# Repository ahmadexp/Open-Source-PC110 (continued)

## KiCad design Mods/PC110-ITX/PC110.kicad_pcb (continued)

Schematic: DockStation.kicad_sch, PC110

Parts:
C1: DNP; C_0402_1005Metric; not fitted
C2, C235, C237, C239, C265: 150nF; C_0402_1005Metric
C3, C7, C91, C93: 100nF; C_0402_1005Metric
C4: 1nF; C_0402_1005Metric
C86, C88: 180nF; C_0402_1005Metric
C89: 470nF; C_0603_1608Metric
C90, C92, C198, C243: 120nF; C_0402_1005Metric
C163, C167, C170, C199: 220pF; C_0402_1005Metric
C168, C238: 1uF; C_0603_1608Metric
C197, C240: 300nF; C_0603_1608Metric
C200, C201: 10uF; C_1206_3216Metric
C202: 150nF; C_0603_1608Metric
D1: 3D
D39, D55: s.3 5F; Diode
D52, D53, D54, D56, D57: K; SOT-416
D59: 3D; SOT-416L
EM5: R-array
F2: 1.0A; Fuse_1206_3216Metric
F3: 0.5A; Fuse_1206_3216Metric
J1: PS2
J8: Modem-Connector
J13: Docking Port
L1: 1.5uH; L_0603_1608Metric
L12: 300nH; L_0805_2012Metric
Q24: 6D; SOT-23
Q25, Q33, Q34: BH RT; SOT-89-3
Q32: 8B; SOT-416
R4: 4.7k; R_0402_1005Metric
R8: 300; R_0402_1005Metric
R122, R123, R124, R125, R127, R130, R135, R139, R144, R183, R187, R189, R190, R191, R194, R228, R302, R303, R305, R306, R307, R309, R311: 470k; R_0402_1005Metric
R181, R188, R192, R193, R289: 10k; R_0402_1005Metric
R230: 0; R_0805_2012Metric
R231: 0; R_0603_1608Metric
R238: 56; R_0603_1608Metric
R241: 8.2; R_1206_3216Metric_Pad1.30x1.75mm_HandSolder
R242: 7.5k; R_0402_1005Metric
R291, R297: 220; R_0402_1005Metric
R293: 22k; R_0402_1005Metric
R294: 1.2k; R_0402_1005Metric
RA2: 10k; R-array
U1: EA; SOT-353
U2: 7W32; sso-8
U3: HSDL-1000 X03; IRDA
U20: 7W14; sso-8
U26: 7W126; sso-8
U57: SN74LVT125; TSSOP-14_4.4x5mm_P0.65mm
U64: SN74LV126; TSSOP-14_4.4x5mm_P0.65mm
U71: SN74LV32; TSSOP-14_4.4x5mm_P0.65mm

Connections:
Dock_PWR_IN-: J13.53 (J13_53), J13.54 (J13_53), J13.55 (J13_53), J13.56 (J13_53), J13.57 (J13_53); also elsewhere on the board
EN_RS232: J13.79 (EN_RS232); also elsewhere on the board
Enable_IRDA_Buf: Q24.1 (B), R242.2, U26.1 (C), U26.7 (~PRE), U57.4, U57.10; also elsewhere on the board
FDC_ACK#: J13.71 (ACK#); also elsewhere on the board
FDC_AUTOFD#: J13.73 (AUTOFD#); also elsewhere on the board
FDC_BUSY: J13.22 (BUSY); also elsewhere on the board
FDC_CTS1#: J8.8 (CTS1#), R191.1; also elsewhere on the board
FDC_CTS2#: J13.82 (CTS2#), R303.2; also elsewhere on the board
FDC_DCD1#: J8.4 (DCD1#), R187.1; also elsewhere on the board
FDC_DCD2#: J13.17 (DCD2#), R309.2; also elsewhere on the board
FDC_DIR#: J13.7 (FDC_DIR#); also elsewhere on the board
FDC_DRATE0: R302.2, U57.2; also elsewhere on the board
FDC_DRATE1: R306.2, U57.12; also elsewhere on the board
FDC_DSKCHG#: J13.12 (FDC_DSKCHG#), R122.2; also elsewhere on the board
FDC_DSR1: J8.7 (DSR1), R189.1; also elsewhere on the board
FDC_DSR2#: J13.84 (DSR2#), R305.2; also elsewhere on the board
FDC_DTR1#: R192.1, U64.9; also elsewhere on the board
FDC_DTR2#: J13.20 (DTR2#); also elsewhere on the board
FDC_ERROR#: J13.77 (ERROR#); also elsewhere on the board
FDC_HDSEL#: J13.11 (FDC_HDSEL#); also elsewhere on the board
FDC_INIT#: J13.72 (INIT#); also elsewhere on the board
FDC_IRRX_RXD2: U26.3 (~Q), U57.8; also elsewhere on the board
FDC_IRTX_TXD2: R183.2, U26.2 (D), U57.5; also elsewhere on the board
FDC_PD0: J13.30 (PD0); also elsewhere on the board
FDC_PD1: J13.29 (PD1); also elsewhere on the board
FDC_PD2: J13.28 (PD2); also elsewhere on the board
FDC_PD3: J13.27 (PD3); also elsewhere on the board
FDC_PD4: J13.26 (PD4); also elsewhere on the board
FDC_PD5: J13.25 (PD5); also elsewhere on the board
FDC_PD6: J13.76 (PD6); also elsewhere on the board
FDC_PD7: J13.24 (PD7); also elsewhere on the board
FDC_PE: J13.78 (PE); also elsewhere on the board
FDC_RDATA#: J13.91 (FDC_RDATA#), R307.2; also elsewhere on the board
FDC_RI1#: J8.5 (RI1#), R190.1; also elsewhere on the board
FDC_RI2#: J13.81 (RI2#), R311.1; also elsewhere on the board
FDC_RTS1#: R193.1, U64.5; also elsewhere on the board
FDC_RTS2#: J13.83 (RTS2#); also elsewhere on the board
FDC_RXD1: J8.10 (RXD1), R194.1; also elsewhere on the board
FDC_SLCT: J13.23 (SLCT); also elsewhere on the board
FDC_SLCTIN#: J13.74 (SLCTIN#); also elsewhere on the board
FDC_STEP#: J13.94 (FDC_STEP#); also elsewhere on the board
FDC_STROBE#: J13.31 (STROBE#); also elsewhere on the board
FDC_TRK0#: J13.9 (FDC_TRK0), R124.2; also elsewhere on the board
FDC_TXD1: R188.1, U64.2; also elsewhere on the board
FDC_TXD2_EN: R8.1, U2.5, U57.6
FDC_UART1_EN: U64.1, U64.4, U64.10; also elsewhere on the board
FDC_WDATA#: J13.8 (FDC_WDATA#); also elsewhere on the board
FDC_WGATE#: J13.93 (FDC_WGATE#); also elsewhere on the board
FDC_WRTPRT#: J13.10 (FDC_WRTPRT#), R125.1; also elsewhere on the board
FDD_Bowman: J13.90 (FDD_Bowman), R144.2; also elsewhere on the board
FDD_DRSEL: J13.5 (FDD_DRSEL); also elsewhere on the board
FDD_INDEX#: J13.4 (FDD_INDEX#), R123.2; also elsewhere on the board
FDD_MOTEN: J13.6 (FDD_MOTEN); also elsewhere on the board
FDD_Pluto1: J13.98 (FDD_Pluto1); also elsewhere on the board
FDD_Pluto2: J13.97 (FDD_Pluto2); also elsewhere on the board
FDD_Pluto3: J13.95 (FDD_Pluto3); also elsewhere on the board
FDD_Pluto4: J13.92 (FDD_Pluto4); also elsewhere on the board
GND: C1.1 (+), C2.2 (-), C3.2 (-), C4.2 (-), C7.2 (-), C86.2 (-), C88.1 (+), C90.1 (+), C91.2 (-), C92.1 (+), C93.2 (-), C163.1 (+), C167.1 (+), C168.1 (+), C170.2 (-), C197.1 (+), C198.2 (-), C199.2 (-), C200.1 (+), C201.2 (-), C202.1 (+), C235.2 (-), C237.2 (-), C239.1 (+), C243.2 (-), C265.1 (+), D52.1 (A), D53.1 (A), D54.1 (A), D56.1 (A), D57.1 (A), J8.1 (GND), J8.13 (GND), J8.14 (GND), J8.26 (GND), J13.1 (GND), J13.50 (GND), J13.51 (GND), J13.64 (GND), J13.66 (GND), J13.68 (GND), J13.70 (GND), J13.75 (GND), J13.85 (GND), J13.100 (GND), Q32.2 (E), R230.1, R231.1, U1.3 (GND), U2.4 (GND), U3.2 (GND), U20.4 (GND), U26.4 (GND), U57.7 (GND), U64.7 (GND), U71.4, U71.5, U71.7 (GND); also elsewhere on the board
KB_INIT1: EM5.5, J13.14 (KB_INT1), RA2.5 (R4.2); also elsewhere on the board
KB_INIT2: EM5.6, J13.15 (KB_INT2), RA2.6 (R3.2); also elsewhere on the board
KB_INIT3: EM5.8, J13.86 (KB_INT3), RA2.8 (R1.2); also elsewhere on the board
KB_INIT4: EM5.7, J13.87 (KB_INT4), RA2.7 (R2.2); also elsewhere on the board
KB_SPKUP_DN: J13.63 (KB_SPKUP_DN); also elsewhere on the board
KB_SRDY#_shift: R294.1; also elsewhere on the board
M38_P16_R86: J13.62 (M38_P16); also elsewhere on the board
M38_P34: J13.38 (M38_P34); also elsewhere on the board
M38_P46: J13.39 (M38_P46); also elsewhere on the board
M38_P67: J13.61 (M38_P67); also elsewhere on the board
MN192_VSEN#: J8.16 (VSEN#); also elsewhere on the board
MN195_U1RD#: J8.3 (U1RD#); also elsewhere on the board
Modem_Audio_Out: C89.1 (+); also elsewhere on the board
Modem_VSDA#: J8.17 (VSDA#), R127.1; also elsewhere on the board
unnamed: C1.2 (-), U2.1, U3.1 (IRDA_RXA)
unnamed: C4.1 (+), D1.1 (A), D1.3 (A), R4.1, U1.2
unnamed: C7.1 (+), J1.7 (PS2_Pluto), L1.2
unnamed: C89.2 (-), J8.18 (VPCK#)
unnamed: C92.2 (-), F3.1, J13.16 (PS/2_Power), L12.1, RA2.1 (R1.1), RA2.2 (R2.1), RA2.3 (R3.1), RA2.4 (R4.1)
unnamed: C163.2 (-), EM5.3, J1.6 (KB_INIT2)
unnamed: C167.2 (-), EM5.4, J1.2 (KB_INIT1)
unnamed: C168.2 (-), U3.3 (PIN_Bypass)
unnamed: C170.1 (+), EM5.1, J1.5 (KB_INIT3)
unnamed: C197.2 (-), U3.5 (Daylight_Cancellation)
unnamed: C198.1 (+), J1.4 (5V), L12.2
unnamed: C199.1 (+), EM5.2, J1.3 (KB_INIT4)
unnamed: C200.2 (-), R241.1, U3.8 (IRDA_LED_A)
unnamed: C201.1 (+), C202.2 (-), R238.1, U3.6 (IRDA_Supply)
unnamed: C238.1 (+), Q33.1 (B), R293.1, R297.2
unnamed: C93.1 (+), C238.2 (-), C239.2 (-), J13.13 (FDD_PWR), J13.88 (FDD_PWR), J13.89 (FDD_PWR), Q33.2 (C)
unnamed: C240.1 (+), Q34.1 (B), R294.2
unnamed: C240.2 (-), F3.2, Q34.2 (C)
unnamed: D1.2 (K), R4.2, U2.3
unnamed: D39.2 (A), D55.2 (A), J13.46 (PNET4), J13.48 (PNET4)
unnamed: J1.1 (GND), R231.2
unnamed: J1.8 (GND), R230.2
unnamed: J8.6 (DRT1#), U64.8
unnamed: J8.9 (RTS1#), U64.6
unnamed: J8.11 (TXD1), U64.3
unnamed: J13.96 (FDD_DRATE0), U57.3
unnamed: J13.3 (FDD_DRATE1), U57.11
unnamed: J8.21 (ADCK#), J13.59 (Modem_ADCK#)
unnamed: J8.20 (IRQ1#), J13.60 (Modem_IRQ1#)
unnamed: J8.24 (RSRVD2), J13.42 (Modem_RSRVD1)
unnamed: J8.23 (RSRVD1), J13.41 (Modem_RSRVD2)
unnamed: J8.22 (S11), J13.58 (Modem_S11)
unnamed: J8.19 (VPDA#), J13.52 (Modem_VPDA#)
unnamed: J13.18 (RXD2), R135.1, U26.5 (Q)
unnamed: J13.19 (TXD2), U26.6 (~CLR)
unnamed: Q24.3 (C), R238.2
unnamed: Q25.1 (B), R242.1
unnamed: Q25.2 (C), R241.2
unnamed: Q32.1 (B), R289.2
unnamed: Q32.3 (C), R291.1
unnamed: F2.1, Q33.3 (E), R293.2
unnamed: R289.1, U20.2
unnamed: R291.2, R297.1
unnamed: U1.4, U2.2
unnamed: U2.7, U57.9
unnamed: R8.2, U3.7 (IRDA_TXD)
unnamed: U20.6, U57.1, U57.13, U71.3
PNET1: D52.2 (K), D53.2 (K), D54.2 (K), D56.2 (K), D57.2 (K), R127.2, R228.1, U64.14 (VCC); also elsewhere on the board
PNET2: C2.1 (+), C3.1 (+), C235.1 (+), C237.1 (+), J13.21 (PNET2), J13.80 (PNET2), R183.1, U1.5 (VCC), U2.8 (VCC); also elsewhere on the board
PNET4: D39.1 (K), D55.1 (K); also elsewhere on the board
PNET5: C90.2 (-), C91.1 (+), C243.1 (+), C265.2 (-), F2.2, J13.40 (PNET5), Q24.2 (E), Q25.3 (E), Q34.3 (E), R122.1, R123.1, R124.1, R125.2, R135.2, R188.2, R192.2, R193.2, R302.1, R303.1, R305.1, R306.1, R307.1, R309.1, R311.2, U20.8 (VCC), U26.8 (VCC), U57.14 (VCC), U71.14 (VCC); also elsewhere on the board
PNET7: R130.1, R139.1, R144.1; also elsewhere on the board
PS2_L1_Pluto: L1.1, R228.2; also elsewhere on the board
PWRGD_shift_buff: R181.2, U71.1; also elsewhere on the board
Pluto_Dock_IO1: J13.2 (Pluto_Dock1), R139.2; also elsewhere on the board
Pluto_Dock_IO2: J13.99 (Pluto_Dock2), R130.2; also elsewhere on the board
Pluto_IRDA_OUT: U2.6; also elsewhere on the board
Pluto_Switched_PNET5: C86.1 (+), J8.12 (PNET5_Pluto), J8.15 (PNET5_Pluto), R187.2, R189.2, R190.2, R191.2, R194.2; also elsewhere on the board
U71_OR1_IN2: U71.2; also elsewhere on the board
VCC: C88.2 (-), J8.2 (VCC), J8.25 (VCC); also elsewhere on the board
VGA_Blue: D54.3 (COM), J13.65 (VGA_Blue); also elsewhere on the board
VGA_Green: D53.3 (COM), J13.67 (VGA_Green); also elsewhere on the board
VGA_HSync: D56.3 (COM), J13.36 (VGA_HSync); also elsewhere on the board
VGA_Red: D52.3 (COM), J13.69 (VGA_Red); also elsewhere on the board
VGA_VSync: D57.3 (COM), J13.33 (VGA_VSync); also elsewhere on the board
YellowWire1_2: R181.1; also elsewhere on the board

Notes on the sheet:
YellowWire2_2
YellowWire2_3
YellowWire2_1
Enables all external PS/2 devices; PS/2 conn on PC110 and dock

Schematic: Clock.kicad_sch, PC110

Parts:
C56, C242: 100nF; C_0402_1005Metric
C59: 10nF; C_0603_1608Metric
C227, C256: 150nF; C_0402_1005Metric
C230, C257, C261: DNP; C_0402_1005Metric; not fitted
C232: 10uF; C_1206_3216Metric
C254, C260: 1nF; C_0402_1005Metric
C258: 220pF; C_0402_1005Metric
C259: 330nF; C_0603_1608Metric
D9: DNP; 3D; not fitted
Q31: 6D; SOT-23
R79: 0; R_0402_1005Metric
R91: 470k; R_0402_1005Metric
R275: 4.7k; R_0402_1005Metric
R284: 10; R_0805_2012Metric
R332, R340, R341, R348, R350, R357, R359: 33; R_0402_1005Metric
R344: DNP; R_0402_1005Metric; not fitted
R353: 56; R_0402_1005Metric
R358: 47; R_0402_1005Metric
U16: 8C01; SOT-23-5
U62: SN74LVT125; TSSOP-14_4.4x5mm_P0.65mm
U63: AV9154A-27; SOIC-16W
U66: SN74LV02; TSSOP-14_4.4x5mm_P0.65mm
X4: 59G3482; XTAL-6

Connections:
Bowman_CLK: R340.2; also elsewhere on the board
Chipset_2XCPU_CLK: R359.2; also elsewhere on the board
Chipset_CLK: R341.1; also elsewhere on the board
ESS_CLK: R344.2; also elsewhere on the board
FDC_CLK: R332.2; also elsewhere on the board
GND: C56.2, C59.2, C227.1 (+), C230.1 (+), C232.1 (+), C242.1 (+), C254.1 (+), C256.1 (+), C258.1 (+), C259.1 (+), C260.1 (+), C261.2 (-), R91.2, R275.2, U16.3 (GND), U62.1, U62.4, U62.7 (GND), U62.10, U62.13, U63.5 (GND), U63.8 (AGND), U63.12 (GND), U63.15 (FS1), U66.7 (GND), X4.3; also elsewhere on the board
unnamed: C227.2 (-), D9.2 (K), Q31.3 (C), R79.1, R275.1, R284.1, U63.10 (FS2), U63.16 (FS0)
unnamed: C230.2 (-), C257.2 (-), U63.2 (X2), X4.2
unnamed: C232.2 (-), C258.2 (-), C259.2 (-), C260.2 (-), R284.2, U63.4 (VCC), U63.13 (VCC)
unnamed: C257.1 (+), C261.1 (+), U63.3 (X1), X4.1
unnamed: Q31.1 (B), U66.13
unnamed: R332.1, R340.1, U62.8
unnamed: R341.2, R348.2, U62.6
unnamed: R344.1, R353.1, U62.11
unnamed: R350.2, U62.3
unnamed: R357.1, U62.2, U62.5, U62.12
unnamed: R358.1, U62.9
unnamed: C59.1, D9.3 (A), U16.5 (CD)
unnamed: R91.1, U16.1 (OUT), U63.9 (OE)
unnamed: C56.1, D9.1 (A), R79.2, U16.2 (VDD)
unnamed: R359.1, U63.14 (3XCPUCLK)
unnamed: R357.2, U63.11 (14.318MHz)
unnamed: R358.2, U63.6 (24MHz)
PNET1: C242.2 (-), C254.2 (-), C256.2 (-), Q31.2 (E), U62.14 (VCC), U66.14 (VCC); also elsewhere on the board
PWRGD: U66.12; also elsewhere on the board
Pluto_CLK: R348.1; also elsewhere on the board
RESET: U66.11; also elsewhere on the board
VGA_CLK: R350.1; also elsewhere on the board
YMF_CLK: R353.2; also elsewhere on the board

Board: 10 copper layers, 935 parts (731 on the bottom side), 1140 nets, no tracks yet.

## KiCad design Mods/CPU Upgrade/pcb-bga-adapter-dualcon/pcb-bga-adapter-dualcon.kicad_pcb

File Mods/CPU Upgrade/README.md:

## Related Works ##

Taka published details of upgrading the CPU on the 230cs.  As the 230cs shares design features with the PC110 ( VL82C420 ),  there is relevance in these works:

https://garakutaen.sakura.ne.jp/thinkpad/ChgCpu230.html

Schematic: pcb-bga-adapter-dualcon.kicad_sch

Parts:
J1: 54722-0604; 547220604; Mouser Part Number 538-54722-0604
J2: 55560-0607; 555600607; Mouser Part Number 538-55560-0607
U1: BGA-256-MIRRORED

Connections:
A2: J1.54, U1.A3 (A2)
A3: J1.48, U1.D2 (A3)
A4: J1.46, U1.D1 (A4)
A5: J1.44, U1.E2 (A5)
A6: J1.42, U1.F2 (A6)
A7: J1.40, U1.F1 (A7)
A8: J1.38, U1.G2 (A8)
A9: J1.36, U1.G1 (A9)
A10: J1.32, U1.H2 (A10)
A11: J1.34, U1.H1 (A11)
A12: J1.30, U1.J1 (A12)
A13: J1.28, U1.K2 (A13)
A14: J1.26, U1.K1 (A14)
A15: J1.24, U1.L2 (A15)
A16: J1.22, U1.L1 (A16)
A17: J1.20, U1.M2 (A17)
A18: J1.18, U1.N1 (A18)
A19: J1.16, U1.P2 (A19)
A20: J1.14, U1.P1 (A20)
A20M#: J2.58, U1.B13 (A20M#)
A21: J1.8, U1.T3 (A21)
A22: J1.10, U1.R3 (A22)
A23: J1.12, U1.P3 (A23)
A24: J1.2, U1.T4 (A24)
A25: J1.4, U1.R4 (A25)
A26: J1.6, U1.P4 (A26)
A27: J1.27, U1.T5 (A27)
A28: J1.25, U1.R5 (A28)
A29: J1.23, U1.P5 (A29)
A30: J1.21, U1.T6 (A30)
A31: J1.1, U1.R6 (A31)
ADS#: J1.52, U1.B3 (ADS#)
AHOLD: J1.59, U1.A8 (AHOLD)
BE0#: J1.33, U1.B10 (BE0#)
BE1#: J1.29, U1.C10 (BE1#)
BE2#: J2.48, U1.A11 (BE2#)
BE3#: J2.50, U1.B11 (BE3#)
BLAST#: J1.50, U1.C3 (BLAST#)
BRDY#: J1.58, U1.B5 (BRDY#)
BS16#: J1.60, U1.A6 (BS16#)
CLK: J1.35, U1.A9 (CLK)
D0: J1.17, U1.R7 (D0)
D1: J1.3, U1.P7 (D1)
D2: J1.5, U1.T8 (D2)
D3: J1.11, U1.R8 (D3)
D4: J1.7, U1.P8 (D4)
D5: J1.13, U1.T9 (D5)
D6: J1.15, U1.R9 (D6)
D7: J1.9, U1.P9 (D7)
D8: J2.4, U1.R10 (D8)
D9: J2.14, U1.P10 (D9)
D10: J2.2, U1.R11 (D10)
D11: J2.8, U1.P11 (D11)
D12: J2.10, U1.T12 (D12)
D13: J2.16, U1.R12 (D13)
D14: J2.12, U1.P12 (D14)
D15: J2.18, U1.T13 (D15)
D16: J2.1, U1.P13 (D16)
D17: J2.5, U1.R16 (D17)
D18: J2.9, U1.P16 (D18)
D19: J2.7, U1.P15 (D19)
D20: J2.13, U1.N16 (D20)
D21: J2.11, U1.N15 (D21)
D22: J2.17, U1.M16 (D22)
D23: J2.15, U1.M15 (D23)
D24: J2.19, U1.L15 (D24)
D25: J2.25, U1.K16 (D25)
D26: J2.23, U1.K15 (D26)
D27: J2.29, U1.J16 (D27)
D28: J2.27, U1.J15 (D28)
D29: J2.33, U1.H16 (D29)
D30: J2.31, U1.H15 (D30)
D31: J2.37, U1.G16 (D31)
DC#: J2.60, U1.A12 (DC#)
DP0: J1.19, U1.T7 (DP0)
DP1: J2.6, U1.T10 (DP1)
DP2: J2.3, U1.R13 (DP2)
DP3: J2.21, U1.L16 (DP3)
EADS#: J2.54, U1.A13 (EADS#)
FLUSH#: J2.49, U1.C16 (FLUSH#)
GND: J2.20, J2.22, J2.24, J2.26, J2.28, J2.30, J2.32, J2.34, J2.36, J2.38, J2.40, J2.42, J2.44, J2.46, U1.F4 (GND), U1.F5 (GND), U1.F6 (GND), U1.F7 (GND), U1.F8 (GND), U1.F9 (GND), U1.F10 (GND), U1.F11 (GND), U1.F12 (GND), U1.F13 (GND), U1.G4 (GND), U1.G5 (GND), U1.G6 (GND), U1.G7 (GND), U1.G8 (GND), U1.G9 (GND), U1.G10 (GND), U1.G11 (GND), U1.G12 (GND), U1.G13 (GND), U1.H4 (GND), U1.H5 (GND), U1.H6 (GND), U1.H7 (GND), U1.H8 (GND), U1.H9 (GND), U1.H10 (GND), U1.H11 (GND), U1.H12 (GND), U1.H13 (GND), U1.J4 (GND), U1.J5 (GND), U1.J6 (GND), U1.J7 (GND), U1.J8 (GND), U1.J9 (GND), U1.J10 (GND), U1.J11 (GND), U1.J12 (GND), U1.J13 (GND), U1.K4 (GND), U1.K5 (GND), U1.K6 (GND), U1.K7 (GND), U1.K8 (GND), U1.K9 (GND), U1.K10 (GND), U1.K11 (GND), U1.K12 (GND), U1.K13 (GND), U1.L4 (GND), U1.L5 (GND), U1.L6 (GND), U1.L7 (GND), U1.L8 (GND), U1.L9 (GND), U1.L10 (GND), U1.L11 (GND), U1.L12 (GND), U1.L13 (GND)
HLDA: J1.37, U1.B9 (HLDA)
HOLD: J1.39, U1.C7 (HOLD)
INTR: J2.45, U1.D15 (INTR)
KEN#: J1.56, U1.B7 (KEN#)
MIO#: J2.56, U1.C11 (MIO#)
NMI: J2.47, U1.D16 (NMI)
RDY#: J1.57, U1.A7 (RDY#)
RESET: J2.52, U1.C13 (RESET)
SMI#: J2.39, U1.F15 (SMI#)
SMIACT#: J2.43, U1.E16 (SMIACT#)
SRESET: J2.41, U1.E15 (SRESET)
STPCLK#: J2.35, U1.G15 (STPCLK#)
VCC: J1.41, J1.43, J1.45, J1.47, J1.49, J1.51, J1.53, J1.55, J2.51, J2.53, J2.55, J2.57, J2.59, U1.D3 (VCC), U1.D4 (VCC), U1.D5 (VCC), U1.D6 (VCC), U1.D7 (VCC), U1.D8 (VCC), U1.D9 (VCC), U1.D10 (VCC), U1.D11 (VCC), U1.D12 (VCC), U1.D13 (VCC), U1.D14 (VCC), U1.E3 (VCC), U1.E4 (VCC), U1.E5 (VCC), U1.E6 (VCC), U1.E7 (VCC), U1.E8 (VCC), U1.E9 (VCC), U1.E10 (VCC), U1.E11 (VCC), U1.E12 (VCC), U1.E13 (VCC), U1.E14 (VCC), U1.F3 (VCC), U1.F14 (VCC), U1.G3 (VCC), U1.G14 (VCC), U1.H3 (VCC), U1.H14 (VCC), U1.J3 (VCC), U1.J14 (VCC), U1.K3 (VCC), U1.K14 (VCC), U1.L3 (VCC), U1.L14 (VCC), U1.M3 (VCC), U1.M4 (VCC), U1.M5 (VCC), U1.M6 (VCC), U1.M7 (VCC), U1.M8 (VCC), U1.M9 (VCC), U1.M10 (VCC), U1.M11 (VCC), U1.M12 (VCC), U1.M13 (VCC), U1.M14 (VCC), U1.N3 (VCC), U1.N4 (VCC), U1.N5 (VCC), U1.N6 (VCC), U1.N7 (VCC), U1.N8 (VCC), U1.N9 (VCC), U1.N10 (VCC), U1.N11 (VCC), U1.N12 (VCC), U1.N13 (VCC), U1.N14 (VCC)
WR#: J1.31, U1.C9 (WR#)

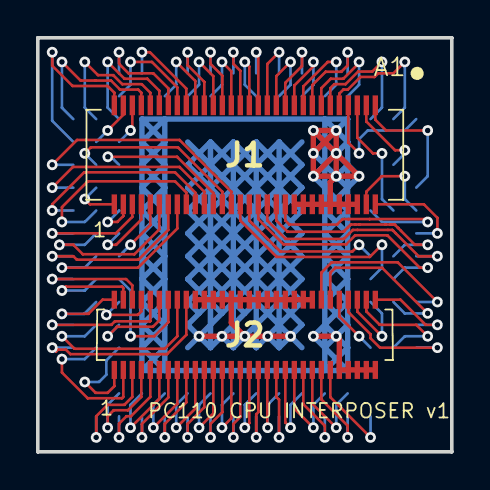
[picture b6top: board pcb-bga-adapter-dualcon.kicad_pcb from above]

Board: 2 copper layers, 23.0 x 23.0 mm, 3 parts (1 on the bottom side), 95 nets.

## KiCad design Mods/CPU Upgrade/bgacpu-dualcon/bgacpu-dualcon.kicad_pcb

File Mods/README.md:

# Modifications

> 🗺️ **New here? Start with the [Modernization roadmap](ROADMAP.md)** — a ranked, opinionated list of
> the mods worth doing (with effort/risk, what our reverse engineering already de-risks, and the traps
> and hard limits to know before you plan).

Hardware modifications and redesigns for the IBM PC110 palmtop. Each folder is a self-contained project, mostly KiCad/Altium PCB designs, with its own `README.md` and screenshots.

## Projects

### PC110-ITX
An ITX form factor motherboard that reimplements all of the PC110 components, with the original BGA parts converted to QFP alternatives for easier assembly. Full KiCad project with per-block schematics (Processor, Chipset, ASIC, Memory, ROM, VGA, Audio, PCMCIA, Storage, Power, Clock, Super I/O, Keyboard, Dock). Includes netlist, placement, and 3D render views.

### PC110-ITX-all-in-one
A variant of the ITX board that blends the motherboard and the docking station's PSU board into a single all-in-one design. Same KiCad block structure as PC110-ITX, plus the docking station ports and footprints.

### CPU Upgrade
Work toward upgrading the PC110 CPU using a BGA-to-socket adapter board (`pcb-bga-adapter`, plus dual-connector variants). Includes KiCad adapter projects, datasheets, and 3D models. References Taka's 230cs CPU upgrade, which shares the VL82C420 design with the PC110.

### NewDock
A redesigned docking station as a standalone KiCad project (`DockingStation`).

### RAS4
A modification that enables an extra 4MB of internal RAM by repurposing the `VL_D12` line as `RAS#4` on the schematic. Documented with annotated schematic captures.

### BIOS-Multi-Patcher
`PCPATCH.COM` — one DOS tool that applies (and where possible reverses) every known PC110 BIOS mod from a single menu: **DSTN↔TFT** display, **Windows 256-colour** fix, and **32 MB memory patch enable/remove**. Flash sequence byte-identical to `vpatch`; reflashes only the 96 KB main block (boot block preserved); CS-relative staging + pre-flash verification. **⚠️ VALIDATION REQUIRED** and requires booting from an IBM-marked floppy (12 V VPP interlock — see `Discovery/BIOS-Flash` §7).

### 32MB-Memory-BIOS-Patch
A **firmware** memory-expansion mod: a 17-byte BIOS patch that caps POST's extended-memory count so a PC110 populated beyond the stock 20 MB (e.g. a 16+16 MB module) cold-boots cleanly, without the RC circuit / `DARK2301` warm-boot dance of the classic taka 32 MB hack. Includes a reproducible build script and pre-built 256 KB / 96 KB images, flashable via the PS2GUI/PS2TUI "Flash BIOS" feature. **⚠️ VALIDATION REQUIRED — verified by disassembly + emulator only, never flashed to real hardware.**

### TFT
TFT display replacement work, including the TFT Upgrade Kit's BIOS patch floppy (`BIOS_Patch.img`) and a reproducible form of the same DSTN→TFT video-BIOS patch in [`TFT/bios-patch`](TFT/bios-patch) (builder + 18-byte patch spec, decoded in `Discovery/65535` §6c). **⚠️ VALIDATION REQUIRED**; a reverse TFT→DSTN patch is pending a confirmed unpatched-DSTN dump.

### Altium
The PCB projects converted from KiCad to Altium, to add versatility and make Altium's tooling available to the project.

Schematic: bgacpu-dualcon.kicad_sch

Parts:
J1: 55560-0607; 555600607; Mouser Part Number 538-55560-0607
J2: 54722-0604; 547220604; Mouser Part Number 538-54722-0604
U1: BGA-256

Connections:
A2: J1.8, U1.A3 (A2)
A3: J1.14, U1.D2 (A3)
A4: J1.16, U1.D1 (A4)
A5: J1.18, U1.E2 (A5)
A6: J1.20, U1.F2 (A6)
A7: J1.22, U1.F1 (A7)
A8: J1.24, U1.G2 (A8)
A9: J1.26, U1.G1 (A9)
A10: J1.30, U1.H2 (A10)
A11: J1.28, U1.H1 (A11)
A12: J1.32, U1.J1 (A12)
A13: J1.34, U1.K2 (A13)
A14: J1.36, U1.K1 (A14)
A15: J1.38, U1.L2 (A15)
A16: J1.40, U1.L1 (A16)
A17: J1.42, U1.M2 (A17)
A18: J1.44, U1.N1 (A18)
A19: J1.46, U1.P2 (A19)
A20: J1.48, U1.P1 (A20)
A20M#: J2.4, U1.B13 (A20M#)
A21: J1.54, U1.T3 (A21)
A22: J1.52, U1.R3 (A22)
A23: J1.50, U1.P3 (A23)
A24: J1.60, U1.T4 (A24)
A25: J1.58, U1.R4 (A25)
A26: J1.56, U1.P4 (A26)
A27: J1.33, U1.T5 (A27)
A28: J1.35, U1.R5 (A28)
A29: J1.37, U1.P5 (A29)
A30: J1.39, U1.T6 (A30)
A31: J1.59, U1.R6 (A31)
ADS#: J1.10, U1.B3 (ADS#)
AHOLD: J1.1, U1.A8 (AHOLD)
BE0#: J1.27, U1.B10 (BE0#)
BE1#: J1.31, U1.C10 (BE1#)
BE2#: J2.14, U1.A11 (BE2#)
BE3#: J2.12, U1.B11 (BE3#)
BLAST#: J1.12, U1.C3 (BLAST#)
BRDY#: J1.4, U1.B5 (BRDY#)
BS16#: J1.2, U1.A6 (BS16#)
CLK: J1.25, U1.A9 (CLK)
D0: J1.43, U1.R7 (D0)
D1: J1.57, U1.P7 (D1)
D2: J1.55, U1.T8 (D2)
D3: J1.49, U1.R8 (D3)
D4: J1.53, U1.P8 (D4)
D5: J1.47, U1.T9 (D5)
D6: J1.45, U1.R9 (D6)
D7: J1.51, U1.P9 (D7)
D8: J2.58, U1.R10 (D8)
D9: J2.48, U1.P10 (D9)
D10: J2.60, U1.R11 (D10)
D11: J2.54, U1.P11 (D11)
D12: J2.52, U1.T12 (D12)
D13: J2.46, U1.R12 (D13)
D14: J2.50, U1.P12 (D14)
D15: J2.44, U1.T13 (D15)
D16: J2.59, U1.P13 (D16)
D17: J2.55, U1.R16 (D17)
D18: J2.51, U1.P16 (D18)
D19: J2.53, U1.P15 (D19)
D20: J2.47, U1.N16 (D20)
D21: J2.49, U1.N15 (D21)
D22: J2.43, U1.M16 (D22)
D23: J2.45, U1.M15 (D23)
D24: J2.41, U1.L15 (D24)
D25: J2.35, U1.K16 (D25)
D26: J2.37, U1.K15 (D26)
D27: J2.31, U1.J16 (D27)
D28: J2.33, U1.J15 (D28)
D29: J2.27, U1.H16 (D29)
D30: J2.29, U1.H15 (D30)
D31: J2.23, U1.G16 (D31)
DC#: J2.2, U1.A12 (DC#)
DP0: J1.41, U1.T7 (DP0)
DP1: J2.56, U1.T10 (DP1)
DP2: J2.57, U1.R13 (DP2)
DP3: J2.39, U1.L16 (DP3)
EADS#: J2.8, U1.A13 (EADS#)
FLUSH#: J2.11, U1.C16 (FLUSH#)
GND: J2.16, J2.18, J2.20, J2.22, J2.24, J2.26, J2.28, J2.30, J2.32, J2.34, J2.36, J2.38, J2.40, J2.42, U1.F4 (GND), U1.F5 (GND), U1.F6 (GND), U1.F7 (GND), U1.F8 (GND), U1.F9 (GND), U1.F10 (GND), U1.F11 (GND), U1.F12 (GND), U1.F13 (GND), U1.G4 (GND), U1.G5 (GND), U1.G6 (GND), U1.G7 (GND), U1.G8 (GND), U1.G9 (GND), U1.G10 (GND), U1.G11 (GND), U1.G12 (GND), U1.G13 (GND), U1.H4 (GND), U1.H5 (GND), U1.H6 (GND), U1.H7 (GND), U1.H8 (GND), U1.H9 (GND), U1.H10 (GND), U1.H11 (GND), U1.H12 (GND), U1.H13 (GND), U1.J4 (GND), U1.J5 (GND), U1.J6 (GND), U1.J7 (GND), U1.J8 (GND), U1.J9 (GND), U1.J10 (GND), U1.J11 (GND), U1.J12 (GND), U1.J13 (GND), U1.K4 (GND), U1.K5 (GND), U1.K6 (GND), U1.K7 (GND), U1.K8 (GND), U1.K9 (GND), U1.K10 (GND), U1.K11 (GND), U1.K12 (GND), U1.K13 (GND), U1.L4 (GND), U1.L5 (GND), U1.L6 (GND), U1.L7 (GND), U1.L8 (GND), U1.L9 (GND), U1.L10 (GND), U1.L11 (GND), U1.L12 (GND), U1.L13 (GND)
HLDA: J1.23, U1.B9 (HLDA)
HOLD: J1.21, U1.C7 (HOLD)
INTR: J2.15, U1.D15 (INTR)
KEN#: J1.6, U1.B7 (KEN#)
MIO#: J2.6, U1.C11 (MIO#)
NMI: J2.13, U1.D16 (NMI)
RDY#: J1.3, U1.A7 (RDY#)
RESET: J2.10, U1.C13 (RESET)
SMI#: J2.21, U1.F15 (SMI#)
SMIACT#: J2.17, U1.E16 (SMIACT#)
SRESET: J2.19, U1.E15 (SRESET)
STPCLK#: J2.25, U1.G15 (STPCLK#)
VCC: J1.5, J1.7, J1.9, J1.11, J1.13, J1.15, J1.17, J1.19, J2.1, J2.3, J2.5, J2.7, J2.9, U1.D3 (VCC), U1.D4 (VCC), U1.D5 (VCC), U1.D6 (VCC), U1.D7 (VCC), U1.D8 (VCC), U1.D9 (VCC), U1.D10 (VCC), U1.D11 (VCC), U1.D12 (VCC), U1.D13 (VCC), U1.D14 (VCC), U1.E3 (VCC), U1.E4 (VCC), U1.E5 (VCC), U1.E6 (VCC), U1.E7 (VCC), U1.E8 (VCC), U1.E9 (VCC), U1.E10 (VCC), U1.E11 (VCC), U1.E12 (VCC), U1.E13 (VCC), U1.E14 (VCC), U1.F3 (VCC), U1.F14 (VCC), U1.G3 (VCC), U1.G14 (VCC), U1.H3 (VCC), U1.H14 (VCC), U1.J3 (VCC), U1.J14 (VCC), U1.K3 (VCC), U1.K14 (VCC), U1.L3 (VCC), U1.L14 (VCC), U1.M3 (VCC), U1.M4 (VCC), U1.M5 (VCC), U1.M6 (VCC), U1.M7 (VCC), U1.M8 (VCC), U1.M9 (VCC), U1.M10 (VCC), U1.M11 (VCC), U1.M12 (VCC), U1.M13 (VCC), U1.M14 (VCC), U1.N3 (VCC), U1.N4 (VCC), U1.N5 (VCC), U1.N6 (VCC), U1.N7 (VCC), U1.N8 (VCC), U1.N9 (VCC), U1.N10 (VCC), U1.N11 (VCC), U1.N12 (VCC), U1.N13 (VCC), U1.N14 (VCC)
WR#: J1.29, U1.C9 (WR#)

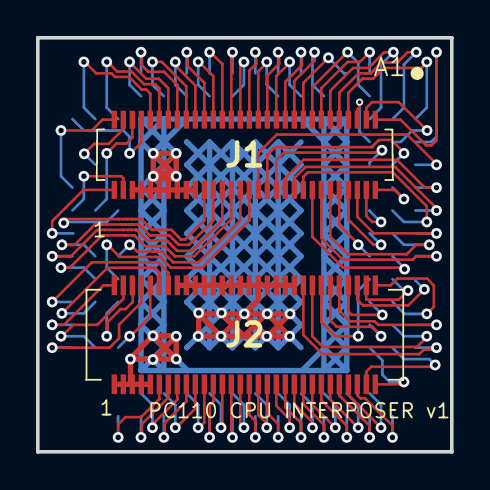
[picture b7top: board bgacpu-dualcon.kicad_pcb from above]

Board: 2 copper layers, 23.0 x 23.0 mm, 3 parts (1 on the bottom side), 95 nets.

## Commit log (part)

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2026-03-17 Add links to images for U75 and U21 components
2026-03-17 Fix formatting of links in README.md
2026-03-17 Fix formatting for U21 Bowman entry in README
2026-03-17 Add image link for Pluto component in README
2026-03-17 Add links for U61 VL82C420FC5 resources
2026-03-18 Add additional links for VL82C420FC5 entry
    Updated links for VL82C420FC5 with additional resources.
2026-03-18 Enhance component entries with more image links
    Updated part details with additional image links for U75, U35, and U21.
2026-03-18 Update U75 entry in components table
2026-05-25 Update README title for U6 firmware disassembly
2026-05-25 Clean up comments in U6_M38223E4HP disassembly
    Removed unnecessary comments from the disassembly file.
2026-05-27 Add images and update description in README.md
2026-06-11 update features
2026-06-14 Add documentation for PC110 CPU debug headers
    Added detailed documentation for PC110 CPU debug headers, including pinouts, usage, limitations, and implementation paths for homebrew debug pods.
2026-06-15 Add initial readme.md for Pluto project
2026-06-15 Fix formatting in readme.md for clarity
2026-06-15 Revise Pluto readme with updated pin details and roles
    Updated pin descriptions and clarified functionality of Pluto in relation to docking station and modem. Confirmed Pluto's roles as floppy controller, serial/dock power manager, and modem control-bus 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
2026-06-15 Document U36 font ROM details in readme
    Added detailed information about U36 font ROM and its contents, including font directory and significance.
2026-06-15 Document U4 (ES488F) audio subsystem analysis
    Added detailed analysis of the U4 (ES488F) audio subsystem, including its architecture, pinout, and associated components.
2026-06-15 Add IBM PC110 Power-On Sequence Repair Guide
    Added a comprehensive repair guide for the IBM PC110 power-on sequence, detailing the power domains, actors involved, troubleshooting steps, and firmware anchors.
2026-06-15 restructure
2026-06-15 update files
2026-06-15 Refactor README for improved clarity and structure
    Updated headings and formatting in the README file.
2026-06-15 Fix punctuation and formatting in README.md
    Corrected punctuation and formatting in the project description and license terms.
